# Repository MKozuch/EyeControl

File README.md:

# EyeControl
An embeded plaftorm for controlling stuff with your eyes and, in the future, maybe the other way around too.

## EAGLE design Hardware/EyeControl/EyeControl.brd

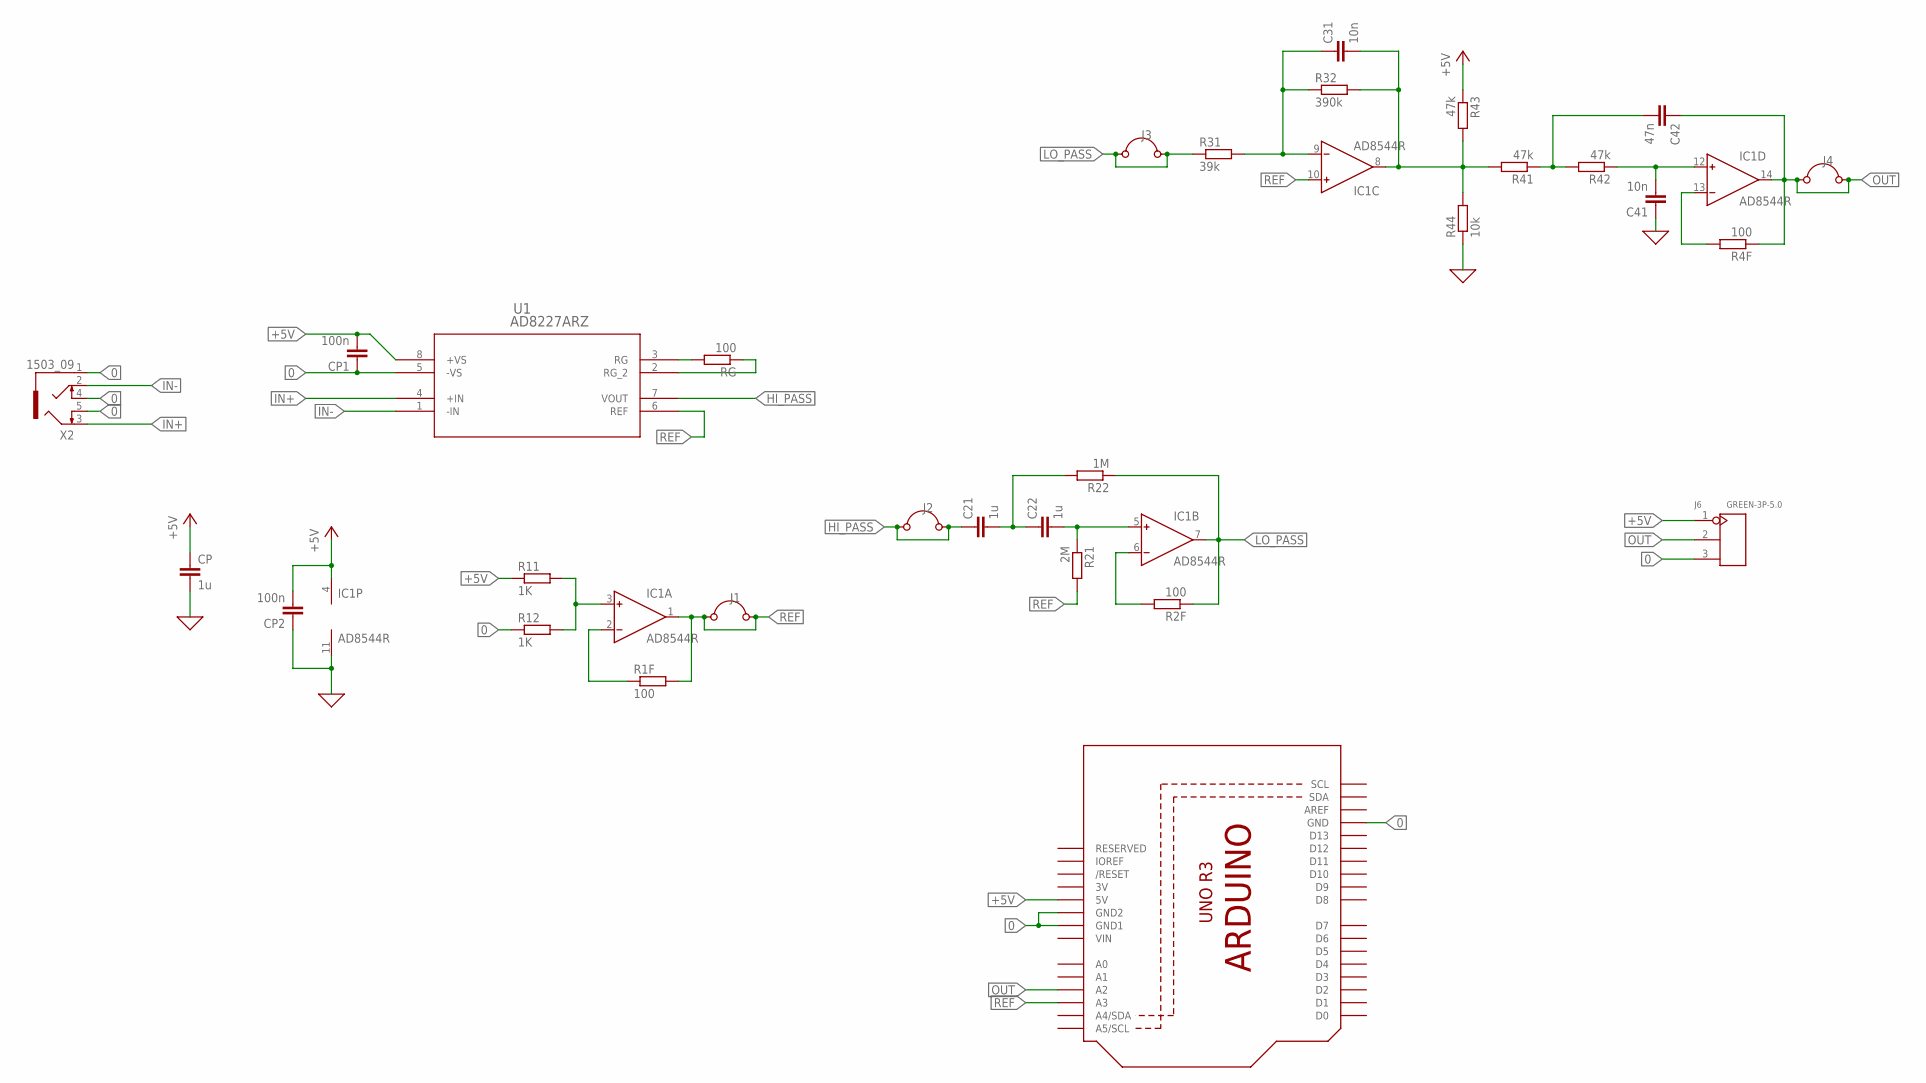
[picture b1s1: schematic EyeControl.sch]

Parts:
C21, C22: 1u; C0805
C31, C41: 10n; C0805
C42: 47n; C0805
CP: 1u; C0805
CP1, CP2: 100n; C0805
IC1: AD8544R; SO14
J1, J2, J3, J4: JUMPER; 05
J6: GREEN-3P-5.0; H3-5.0-15.5X8.0MM
R1F, R2F, R4F: 100; R1206
R11, R12: 1K; R1206
R21: 2M; R1206
R22: 1M; R1206
R31: 39k; R1206
R32: 390k; R1206
R41, R42, R43: 47k; R1206
R44: 10k; R1206
RG: 100; R1206
U1: AD8227ARZ; R_8
U$1: ARDUINOR3-DIMENSION; ARDUINOR3
X2: 1503_09

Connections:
0: C41.1, CP.2, CP1.1, CP2.1, IC1.11 (V-), J6.3, R12.1, R44.1, U1.5 (-VS), U$1.GND, U$1.GND1, U$1.GND2, X2.1, X2.4, X2.5
3V: U$1.3V
+5V: CP.1, CP1.2, CP2.2, IC1.4 (V+), J6.1, R11.1, R43.1, U1.8 (+VS), U$1.5V
HI_PASS: C21.1, J2.1 (+), J2.2 (-), U1.7 (VOUT)
IN+: U1.4 (+IN), X2.3
IN-: U1.1 (-IN), X2.2
LO_PASS: IC1.7 (OUT), J3.1 (+), J3.2 (-), R2F.1, R22.1, R31.1
unnamed: C31.1, IC1.9 (IN-), R31.2, R32.1
unnamed: C41.2, IC1.12 (IN+), R42.1
unnamed: IC1.2 (IN-), R1F.1
unnamed: IC1.3 (IN+), R11.2, R12.2
unnamed: C42.2, R41.1, R42.2
unnamed: C21.2, C22.1, R22.2
unnamed: RG.1, U1.2 (RG_2)
unnamed: RG.2, U1.3 (RG)
unnamed: C22.2, IC1.5 (IN+), R21.1
unnamed: C31.2, IC1.8 (OUT), R32.2, R41.2, R43.2, R44.2
unnamed: IC1.6 (IN-), R2F.2
unnamed: IC1.13 (IN-), R4F.2
OUT: C42.1, IC1.14 (OUT), J4.1 (+), J4.2 (-), J6.2, R4F.1, U$1.A2
REF: IC1.1 (OUT), IC1.10 (IN+), J1.1 (+), J1.2 (-), R1F.2, R21.2, U1.6 (REF), U$1.A3
VIN: U$1.VIN

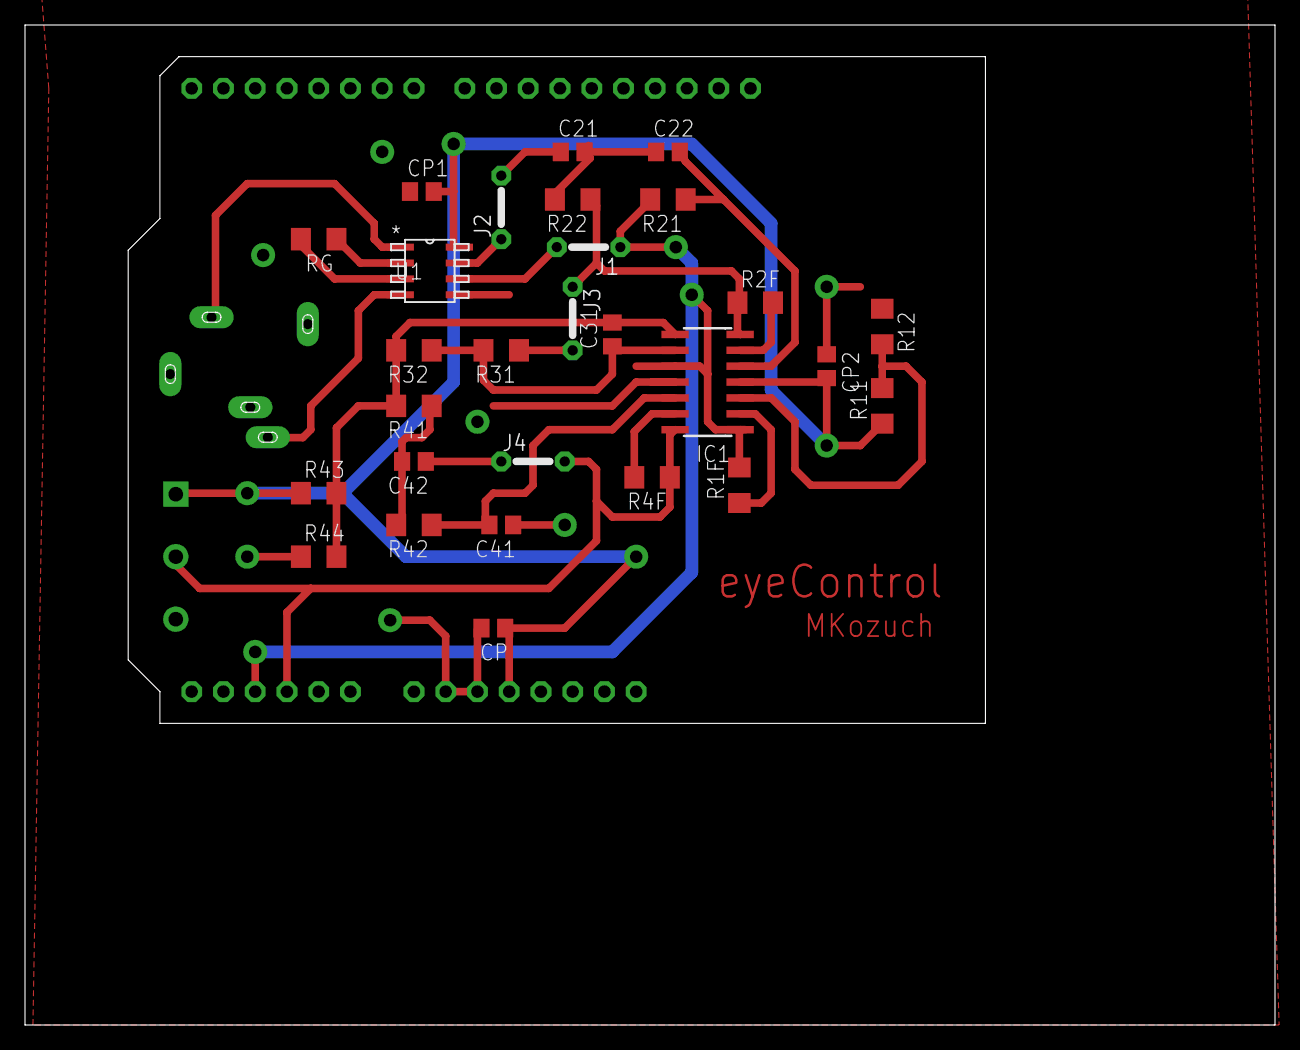
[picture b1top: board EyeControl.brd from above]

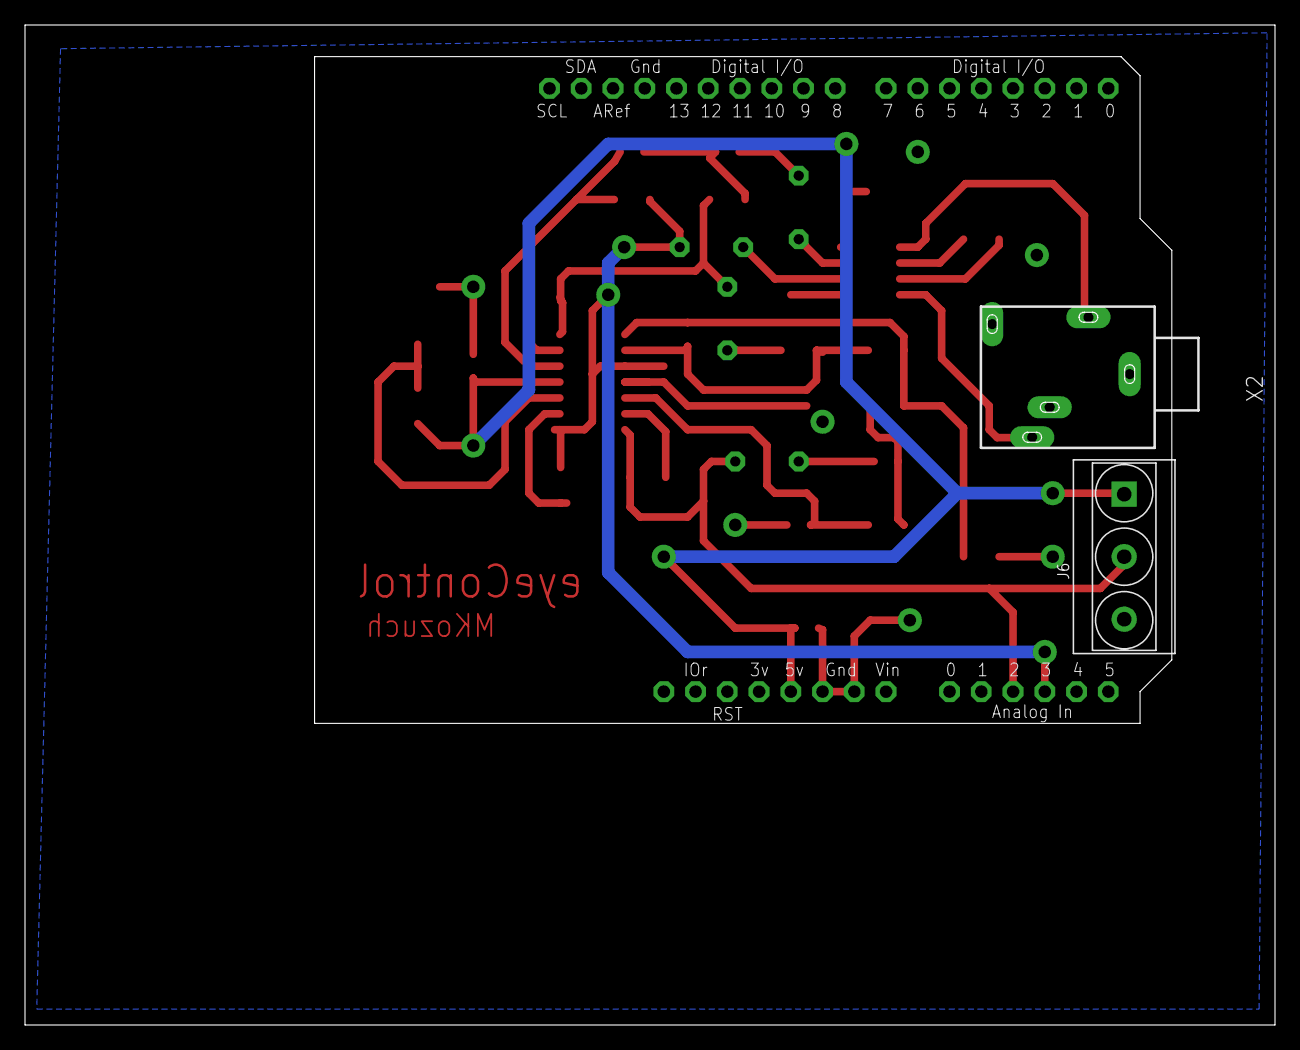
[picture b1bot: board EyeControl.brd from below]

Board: 2 copper layers, 100.0 x 80.0 mm, 31 parts (3 on the bottom side), 20 nets.

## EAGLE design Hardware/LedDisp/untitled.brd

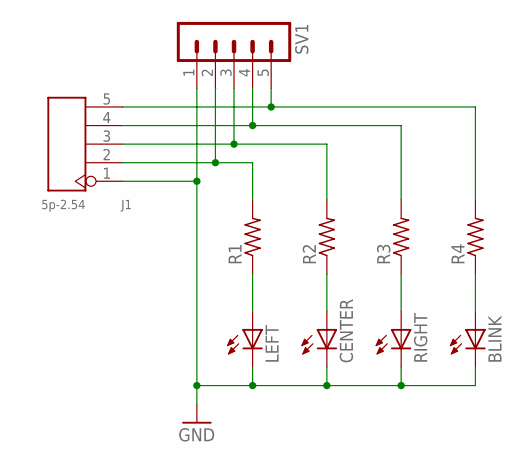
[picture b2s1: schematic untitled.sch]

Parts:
BLINK: LED5MM
CENTER: LED5MM
J1: 5p-2.54; H5-2.54-11.06X6.3MM
LEFT: LED5MM
R1, R2, R3, R4: FLIPFLOP-RES; 0805-THM
RIGHT: LED5MM
SV1: MA05-1

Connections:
GND: BLINK.K (C), CENTER.K (C), J1.1, LEFT.K (C), RIGHT.K (C), SV1.1
unnamed: J1.4, R3.2, SV1.4
unnamed: LEFT.A, R1.1
unnamed: BLINK.A, R4.1
unnamed: R3.1, RIGHT.A
unnamed: CENTER.A, R2.1
unnamed: J1.2, R1.2, SV1.2
unnamed: J1.5, R4.2, SV1.5
unnamed: J1.3, R2.2, SV1.3

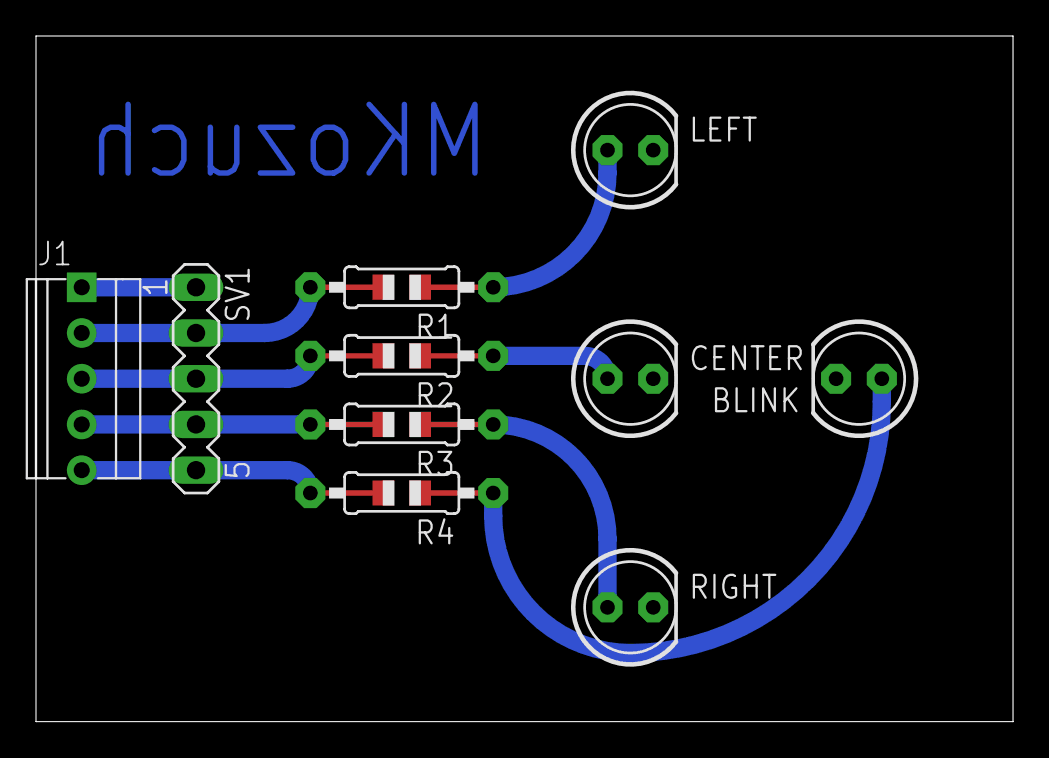
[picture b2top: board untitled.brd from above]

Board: 2 copper layers, 54.3 x 38.1 mm, 10 parts (0 on the bottom side), 9 nets.

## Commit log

2016-04-14 Added files via upload
